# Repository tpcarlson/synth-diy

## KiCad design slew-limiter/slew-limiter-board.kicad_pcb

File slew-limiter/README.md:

# Sloth (Slew Limiter)

##### What is this?

A 4hp dual slew limiter. Slew times are anything from "about the same as the input" to "a few seconds". You can run audio through it or CV - at audio rates it'll act like a really basic low pass filter!

##### How much power does it use?

As measured by the Joranalogue Test 3, around 20 mA on +12v and 10 mA on -12v at peak. The 5v rail is unused.

##### Where does the design come from?

The original schematic is the Dintree D107 "Slew" module (http://www.dintree.com/#D107), with some modifications to allow for state LEDs for the inputs and outputs. There's a thread discussing the modifications on Muffwiggler (https://www.muffwiggler.com/forum/viewtopic.php?f=17&t=243945).

##### Are there any rare/weird parts used?

Nope! All common parts, although the majority of the passives plus the TL074s are SMD. I got my PCBs made and assembled by JLCPCB, but if you've good eyes and some patience the 0805 parts should be solderable by hand.

##### Are there any problems with the design?

This is one of the few modules that has worked perfectly first time! The one minor nit I do have is that the diagram on the front panel came out with the exposed copper a little thin, and the diagram itself is actually inaccurate - the falling edge of the square wave should be followed by the ramp down in copper (Representing the slew limiter output). But, it looks nicer symmetrical, so I'm not going to change it.

The board layout could maybe use a little love - some of the 0805 components are quite close to where you have to solder the audio jacks for example. Functionally, however, it's great.

##### Do you have a BOM/Mouser cart/Tayda links?

Sorry, no. Things go out of stock so frequently it'd be a lot of work to keep these up to date. Everything in this project is easy to source though, so you should not have any trouble.

##### Can I buy PCBs or a kit?

Send me an email (twigathy+synth@gmail.com)...

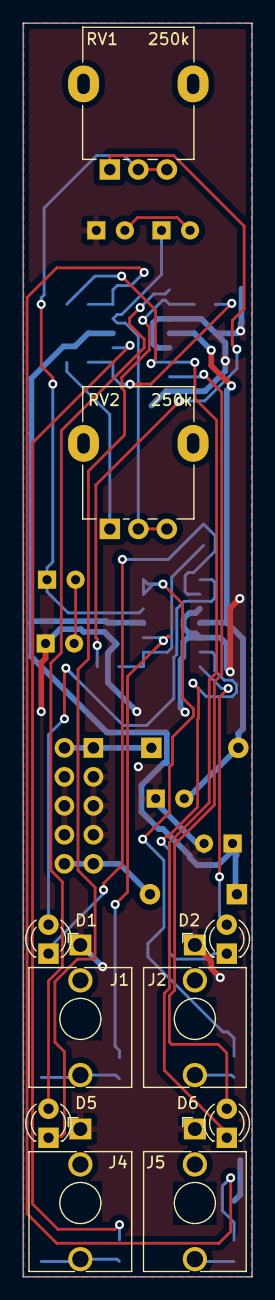
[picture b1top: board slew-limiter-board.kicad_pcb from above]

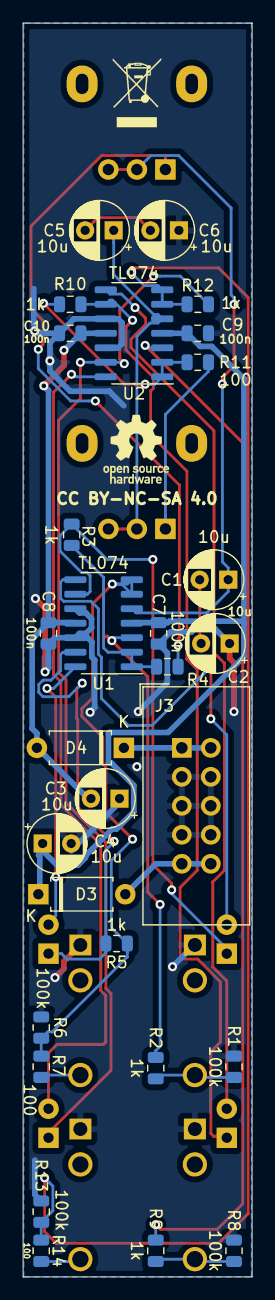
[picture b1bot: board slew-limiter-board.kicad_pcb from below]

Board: 2 copper layers, 20.1 x 109.9 mm, 41 parts (31 on the bottom side), 29 nets.

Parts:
C1, C2, C3, C4, C5, C6: 10u; CP_Radial_D5.0mm_P2.50mm
C7, C8, C9, C10: 100n; C_0805_2012Metric
D1, D2, D5, D6: LED_Dual_2pin; LED_D3.0mm
D3, D4: D_Schottky; D_A-405_P7.62mm_Horizontal
J1, J2, J4, J5: AudioJack2; Jack_3.5mm_QingPu_WQP-PJ398SM_Vertical_CircularHoles
J3: Conn_02x05_Odd_Even; IDC-Header_2x05_P2.54mm_Vertical
J26: WEEE; WEEE-Logo_4.2x6mm_SilkScreen
J27: OSHW; OSHW-Logo_5.7x6mm_SilkScreen
R1, R6, R8, R13: 100k; R_0805_2012Metric
R2, R3, R5, R9, R10, R12: 1k; R_0805_2012Metric
R4, R7, R11, R14: 100; R_0805_2012Metric
RV1, RV2: 250k; Potentiometer_Alpha_RD901F-40-00D_Single_Vertical
U1, U2: TL074; SOIC-14_3.9x8.7mm_P1.27mm

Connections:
+12V: C3.1, C7.1, C9.2, D3.1, U1.4, U2.4
-12V: C4.2, C8.1, C10.2, D4.2, U1.11, U2.11
Earth: C2.1, C3.2, C4.1, C6.1, C7.2, C8.2, C9.1, C10.1, J1.S, J2.S, J3.3, J3.4, J3.5, J3.6, J3.7, J3.8, J4.S, J5.S, R1.1, R6.1, R8.1, R13.1, U1.10, U1.12, U2.10, U2.12
unnamed: C1.1, RV1.2, RV1.3, U1.5
unnamed: C1.2, C2.2
unnamed: C5.1, RV2.2, RV2.3, U2.5
unnamed: C5.2, C6.2
unnamed: D1.1, R3.2, U1.9
unnamed: D1.2, U1.8
unnamed: D2.1, R5.2, U1.13
unnamed: D2.2, U1.14
unnamed: D3.2, J3.9, J3.10
unnamed: D4.1, J3.1, J3.2
unnamed: D5.1, R10.2, U2.9
unnamed: D5.2, U2.8
unnamed: D6.1, R12.2, U2.13
unnamed: D6.2, U2.14
unnamed: J1.T, R1.2, R2.2
unnamed: J2.T, R7.1
unnamed: J4.T, R8.2, R9.2
unnamed: J5.T, R14.1
unnamed: R2.1, U1.3
unnamed: R3.1, R4.2, U1.1, U1.2
unnamed: R4.1, RV1.1
unnamed: R5.1, R6.2, R7.2, U1.6, U1.7
unnamed: R9.1, U2.3
unnamed: R10.1, R11.2, U2.1, U2.2
unnamed: R11.1, RV2.1
unnamed: R12.1, R13.2, R14.2, U2.6, U2.7

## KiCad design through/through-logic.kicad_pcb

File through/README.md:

# Through/Links

##### What is this?

A dual-use module, pretty situational usage! With no jumpers set, this acts as a 1:1 signal distributor, a fancy way of saying "You plug something in on the left hand side and it appears on the right hand side". The panel is double sided which means you may use it either as the 1:1 signal distributor, or as a multiple configured how you want it with jumpers.

I'm using mine as an output to an outboard mixer, with output 1 routing to input 1 on the mixer. This makes connecting signals between the Eurorack and the mixer much easier. I use it like a really tiny patch bay. It might also be helpful for connecting between racks.

##### How much power does it use?

None, this is a passive module

##### Where does the design come from?

This one's all me!

##### Are there any rare/weird parts used?

Nope

##### Are there any problems with the design?

Silkscreen for the multiple panel could be a bit prettier, but otherwise it works fine. If I were to make this an active design (ie. a buffered multiple/signal distributor) I'd probably also add LEDs. As it is, it's fine.

Like all passive multiples, plugging lots of things into this at once with jumpers added will end up with all the outputs and inputs connected together which sometimes can cause problems.

##### Do you have a BOM/Mouser cart/Tayda links?

Sorry, no. Things go out of stock so frequently it'd be a lot of work to keep these up to date. Everything in this project is easy to source though, so you should not have any trouble.

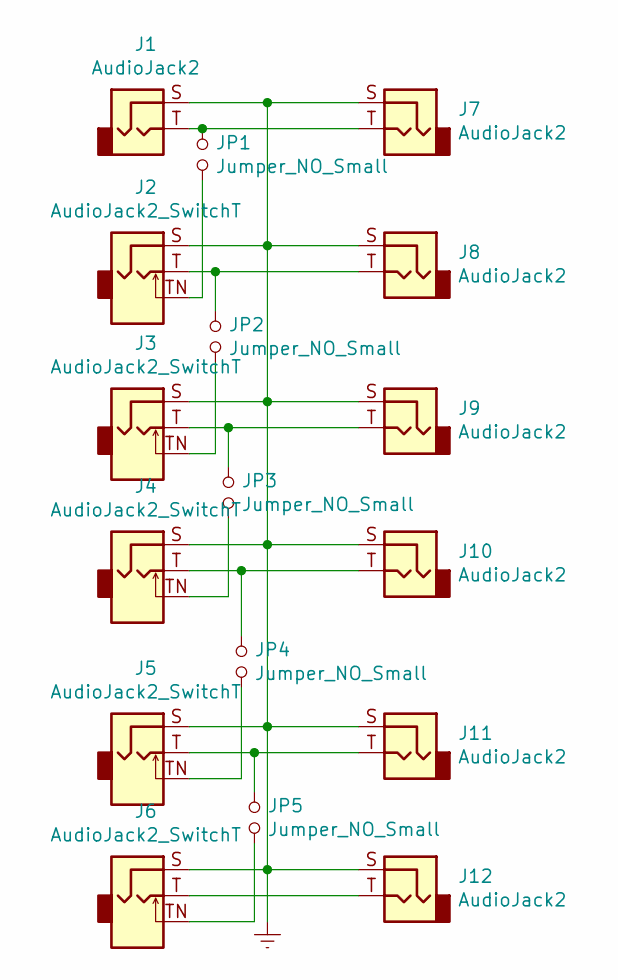
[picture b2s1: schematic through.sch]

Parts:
J1, J7, J8, J9, J10, J11, J12: AudioJack2; Jack_3.5mm_QingPu_WQP-PJ398SM_Vertical_CircularHoles
J2, J3, J4, J5, J6: AudioJack2_SwitchT; Jack_3.5mm_QingPu_WQP-PJ398SM_Vertical_CircularHoles
JP1, JP2, JP3, JP4, JP5: Jumper_NO_Small; PinHeader_1x02_P2.54mm_Vertical

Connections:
Earth: J1.S, J2.S, J3.S, J4.S, J5.S, J6.S, J7.S, J8.S, J9.S, J10.S, J11.S, J12.S
unnamed: J1.T, J7.T, JP1.1
unnamed: J2.T, J8.T, JP2.1
unnamed: J2.TN, JP1.2
unnamed: J3.T, J9.T, JP3.1
unnamed: J3.TN, JP2.2
unnamed: J4.TN, JP3.2
unnamed: J5.TN, JP4.2
unnamed: J6.TN, JP5.2
unnamed: J4.T, J10.T, JP4.1
unnamed: J5.T, J11.T, JP5.1
unnamed: J6.T, J12.T

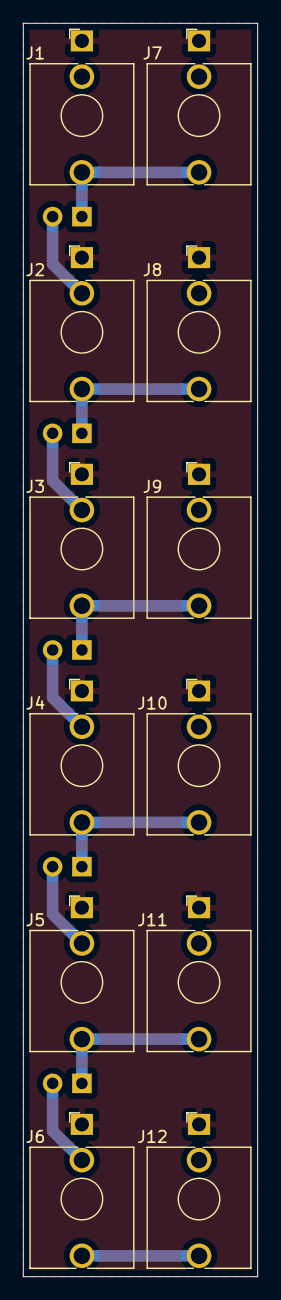
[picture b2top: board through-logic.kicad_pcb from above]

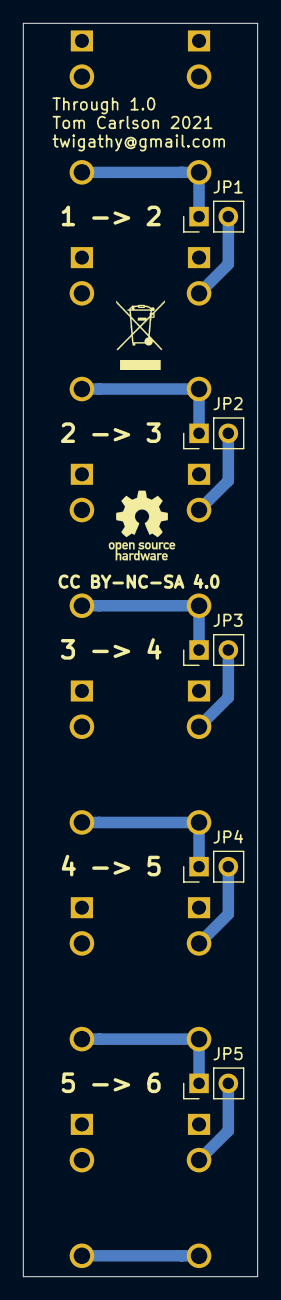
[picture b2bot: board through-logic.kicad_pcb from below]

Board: 2 copper layers, 20.3 x 108.7 mm, 17 parts (5 on the bottom side), 12 nets.

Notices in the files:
slew-limiter/slew-limiter-board.kicad_pcb:
CC BY-NC-SA 4.0
